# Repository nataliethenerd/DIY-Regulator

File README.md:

# DIY Regulator

I have always wanted to make a solder practice board that is actually useful and here it is!

The DIY regulator is a Game Boy Pocket, Color or Pocket Color regulator that provides 5V - meaning it does not work with the OEM screens.

All footprints are the "hand soldered" variants, which makes pads bigger and easier to solder to with a regular hand iron.

# Parts

| Designator | Part             | Footprint | Link |
| ---------- | -----------      | ----      | ---  |
| C2, C3, C4 | 10uF             | 0805      | [Mouser](https://au.mouser.com/ProductDetail/Samsung-Electro-Mechanics/CL21A106KPFNNNG?qs=hqM3L16%252BxldOAmVBBJhBjg%3D%3D) [Digikey](https://www.digikey.com/en/products/detail/samsung-electro-mechanics/CL21A106KPFNNNG/3894419) [LCSC](https://www.lcsc.com/product-detail/C17024.html)     |
| R1         | 100R             | 0603      | [Mouser](https://au.mouser.com/ProductDetail/YAGEO/RC0603FR-07100RL?qs=NEN%2FsE%2FLsvPIwIWKCOS4%2FA%3D%3D) [Digikey](https://www.digikey.com/en/products/detail/yageo/RC0603FR-07100RL/726888) [LCSC](https://www.lcsc.com/product-detail/C105588.html)     |
| L1         | 2.2uH            | 1008      | [Mouser](https://au.mouser.com/ProductDetail/Murata-Electronics/DFE252012F-2R2M%3dP2?qs=ty6qhqyUUEuYhdA0a9%2F0aw%3D%3D) [Digikey](https://www.digikey.com/en/products/detail/murata-electronics/DFE252012F-2R2M-P2/5812591?s=N4IgTCBcDaICIDECiYCsYAMBGMCC0YASmALIgC6AvkA) [LCSC](https://www.lcsc.com/product-detail/C576403.html)     
| U1         | TPS613222A       | SOT-23    | [Mouser](mouser.com/ProductDetail/Texas-Instruments/TPS613222ADBVR) [Digikey](https://www.digikey.com/en/products/detail/texas-instruments/TPS613222ADBVR/8638376) [LCSC](https://www.lcsc.com/product-detail/C2071163.html)     |

# Reading a datasheet

I want part of this project to be a little educational and explain how to read a datasheet and a rough explanation of things.

*DISCLAIMER: I am self taught, so I don't know the physics behind electricity and this might blow up your house (doubt, but it might)*

### Picking the Boost Converter

**TPS613222A** [Data Sheet](https://www.ti.com/lit/ds/symlink/tps61322.pdf)

I chose this boost converter mostly because of the footprint and because I like Texas Instruments parts. I find them very reliable and their datasheets are excellent. 

When you open a datasheet, page one usually has a summery of the part and what it is designed to be used in. This isn't a strict guideline, but helps you get a rough idea if it will be good for your project. 

*perfect! 1-3 NiMh (Ladda, Enloop) or Alkaline (standard AAs)*

Another part of a datasheet you should look at when choosing a part, are the graphs that show how the device performs in under specific conditions. For a Game Boy Color, the original device takes 2xAA batteries in a series. When batteries are in a series, their voltages are added together. 1xAA is 1.5V, so two (that the GBC takes) is 3V. A LiPo operates between 3.3V and 4.2V so it would also perform well with one (this board does not charge it however).

The Game Boy Color will run between 0.1A and 0.3A which is the sweet spot of this part!

### Picking the parts

Staying within the guidelines of the datasheet is best because the results in the datasheet were recorded using these parts. As we do not need over 500mA, we will be following 8.2.1 Boost without Schottky Diode.

## Tests

I tested the DIY Regulator on a Game Boy Color and Game Boy Pocket. 
The tests were completed using Pokemon Red on the Pocket and Pokemon Crystal on the Color. A set of values were collected using the retail carts and a generic flash cart (the kind with a micro sd) Full volume, Q5 HiSpeedido screens and 50% brightness. The results recorded were the mean of values on the title screen using a stock regulator and the DIY Regulator.

### Game Boy Color

### Game Boy Pocket

*note: the cut off on the stock flash value was because the Game Boy Pocket would not boot*

### Result findings

At lower input voltages, there was a much better result using the DIY Regulator - especially on the Pocket. The Pocket is notorious for having a poor regulator. That along with the lower capacity AAA batteries, it often has issues booting a flash cart.

The audio is slightly louder using the DIY Regulator. 

## Thanks

To anyone who has supported me on Patreon - this allows me to make projects like this for everyone

## License

Please do not remove my logo, website and name.

The CC BY-SA 4.0 (Creative Commons Attribution-ShareAlike 4.0 International) license allows you to:

1. **Share** - Copy and redistribute the material in any medium or format.
2. **Adapt** - Remix, transform, and build upon the material for any purpose, even commercially.

### Conditions:

- **Attribution** - You must give appropriate credit, provide a link to the license, and indicate if changes were made. You may do so in any reasonable manner, but not in any way that suggests the licensor endorses you or your use.
- **ShareAlike** - If you remix, transform, or build upon the material, you must distribute your contributions under the same license as the original.

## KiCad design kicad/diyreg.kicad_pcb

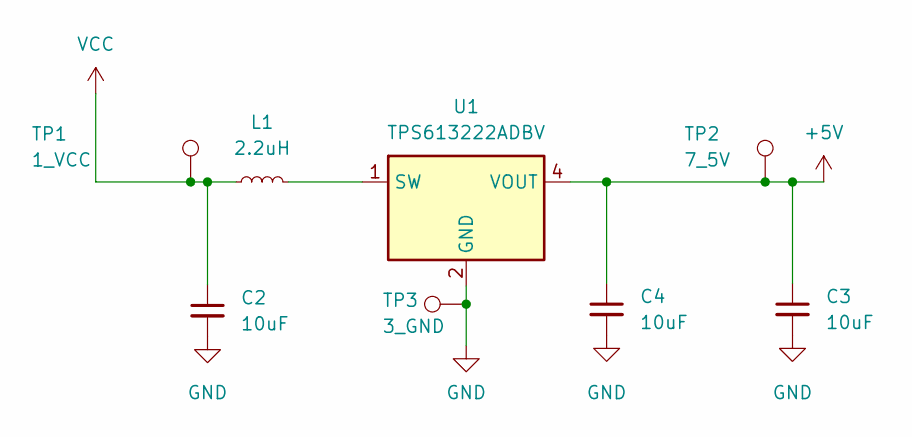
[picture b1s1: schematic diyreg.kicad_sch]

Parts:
C2, C3, C4: 10uF; C_0805_2012Metric_Pad1.18x1.45mm_HandSolder
L1: 2.2uH; L_1008_2520Metric_Pad1.43x2.20mm_HandSolder; Part Number DFE252012F-2R2M=P2
TP1: 1_VCC; TestPoint_THTPad_D2.0mm_Drill1.0mm
TP2: 7_5V; TestPoint_THTPad_D2.0mm_Drill1.0mm
TP3: 3_GND; TestPoint_THTPad_D2.0mm_Drill1.0mm
U1: TPS613222ADBV; SOT-23-5_HandSoldering

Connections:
+5V: C3.1, C4.1, TP2.1 (1_1), U1.4 (VOUT)
GND: C2.2, C3.2, C4.2, TP3.1 (1_1), U1.2 (GND)
unnamed: L1.2, U1.1 (SW)
VCC: C2.1, L1.1, TP1.1 (1_1)

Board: 2 copper layers, 8 parts (8 on the bottom side), 4 nets, no tracks yet.

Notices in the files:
README.md:
License: CC BY-SA 4.0
